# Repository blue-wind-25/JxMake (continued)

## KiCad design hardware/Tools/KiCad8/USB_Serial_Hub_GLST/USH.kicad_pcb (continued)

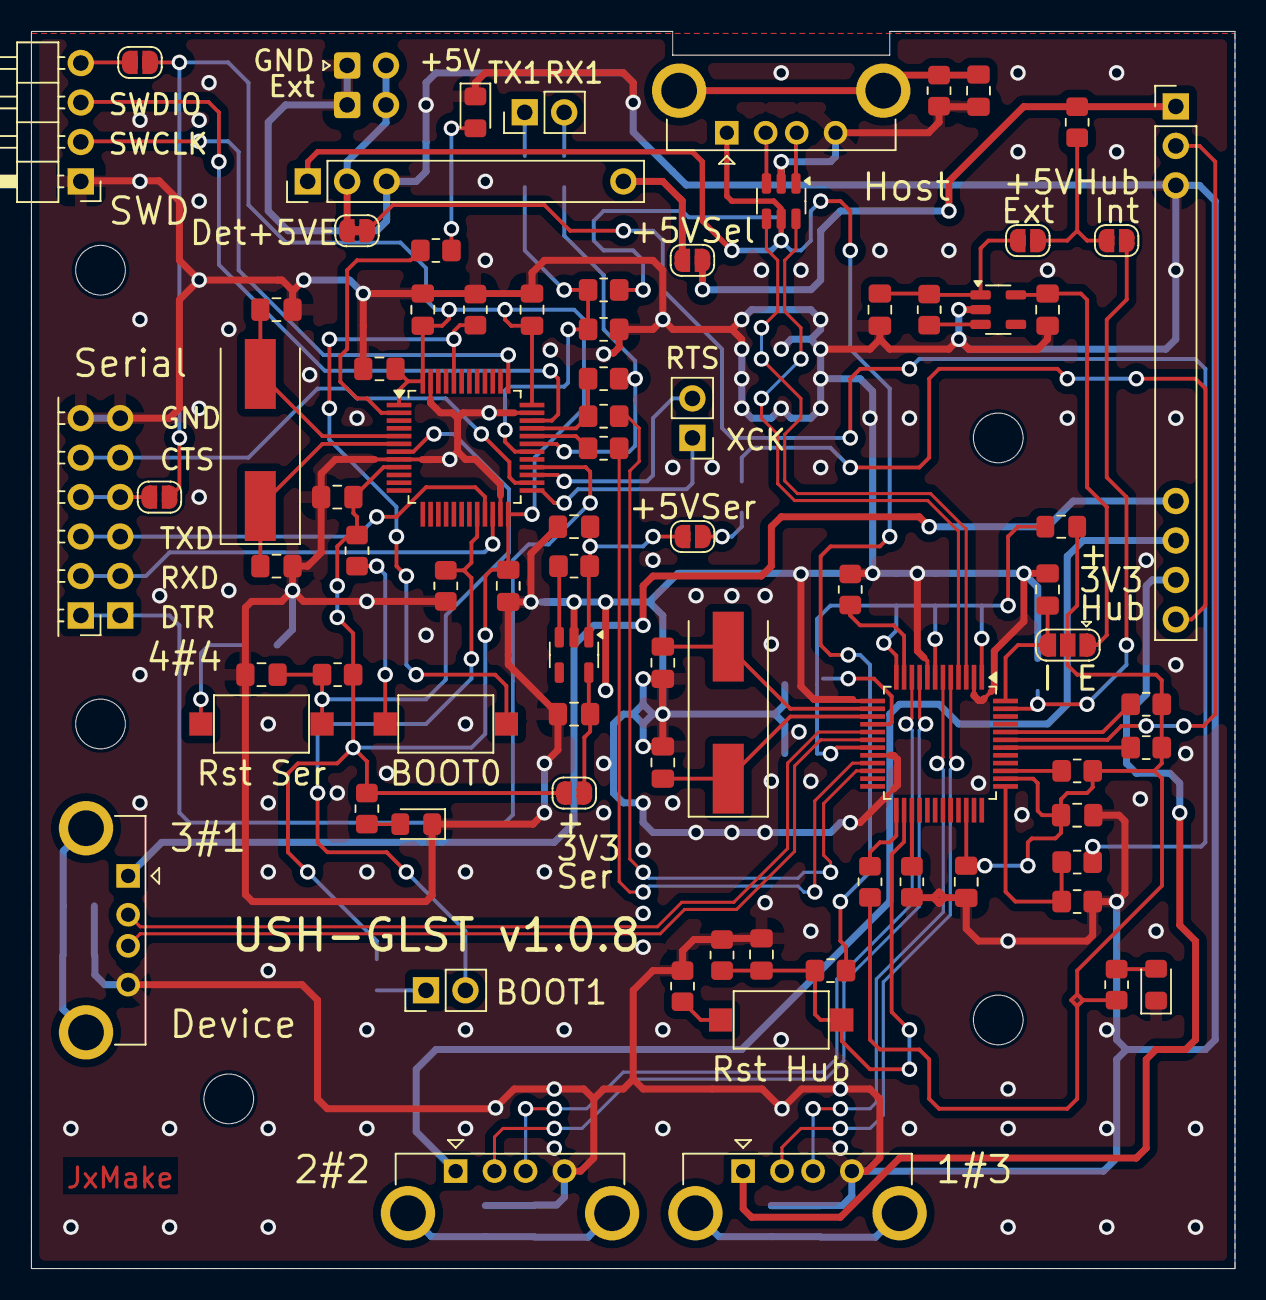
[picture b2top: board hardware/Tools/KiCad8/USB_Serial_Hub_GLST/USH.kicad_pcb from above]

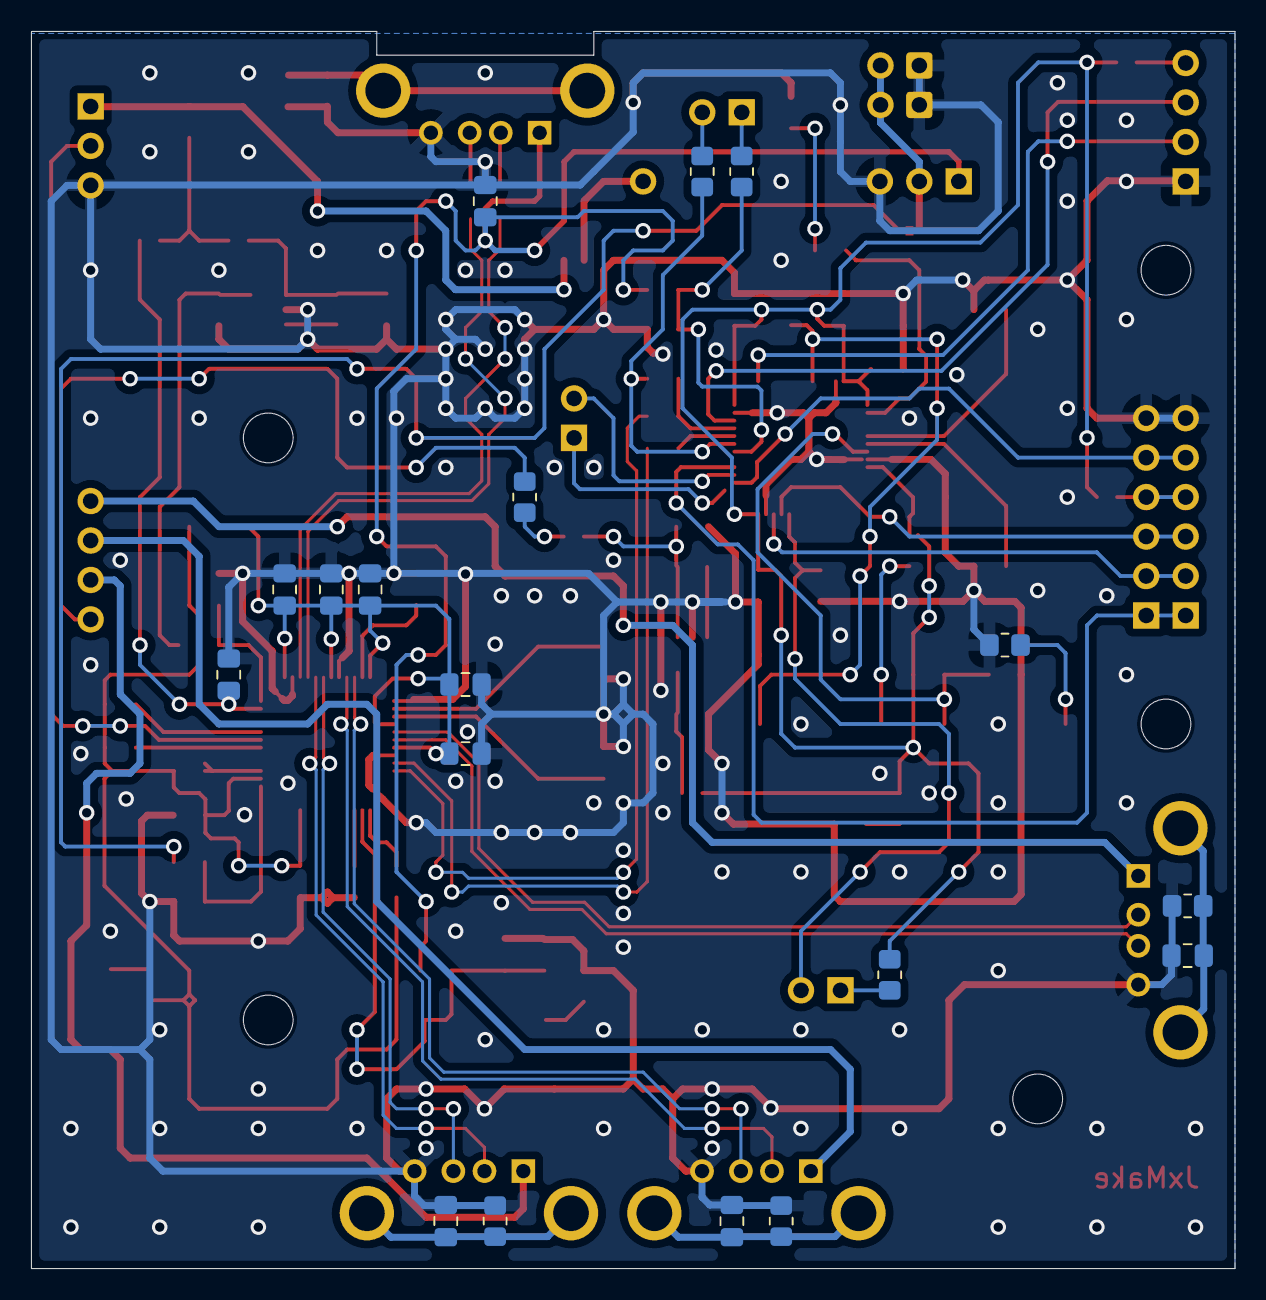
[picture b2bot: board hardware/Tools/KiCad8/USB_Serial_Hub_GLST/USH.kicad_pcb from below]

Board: 2 copper layers, 77.5 x 79.6 mm, 104 parts (19 on the bottom side), 79 nets.
